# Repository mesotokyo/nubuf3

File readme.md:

# MST DRIVE (Nutube Powered Booster/Overdrive) schematic and PCB for KiCAD

(Japanese version is [here](readme_ja.md) / 日本語版は[こちら](readme_ja.md))

## What is this?

KiCAD files to build PCB of the MST DRIVE (Nutube Powered Booster/Overdive). These files are created with KiCad 6.0.

For more information about MST DRIVE, please check https://meso.tokyo/works/drive .

## Notice

 * This schematic and PCB file need a `ak_misc` footprint library in [mst-kicad-lib](https://github.com/mesotokyo/mst-kicad-lib). 
 * It is assumed that this schematic will be used with [voltboost2e](https://github.com/mesotokyo/voltboost2e) DC-DC converter unit.

## DISCLAIMER

FILES IN THIS REPOSITORY ARE PROVIDED "AS IS", WITHOUT WARRANTY OF ANY KIND, EXPRESS OR IMPLIED, INCLUDING BUT NOT LIMITED TO THE WARRANTIES OF MERCHANTABILITY, FITNESS FOR A PARTICULAR PURPOSE AND NONINFRINGEMENT. IN NO EVENT SHALL THE AUTHORS OR COPYRIGHT HOLDERS BE LIABLE FOR ANY CLAIM, DAMAGES OR OTHER LIABILITY, WHETHER IN AN ACTION OF CONTRACT, TORT OR OTHERWISE, ARISING FROM, OUT OF OR IN CONNECTION WITH IN FILES IN THIS REPOSITORY OR THE USE OR OTHER DEALINGS IN FILES IN THIS REPOSITORY.

## License

CC BY 4.0. For more information, please check https://creativecommons.org/licenses/by/4.0/ .

## Author

MST/mesotokyo

 - https://meso.tokyo/
 - https://x.com/mesotokyox

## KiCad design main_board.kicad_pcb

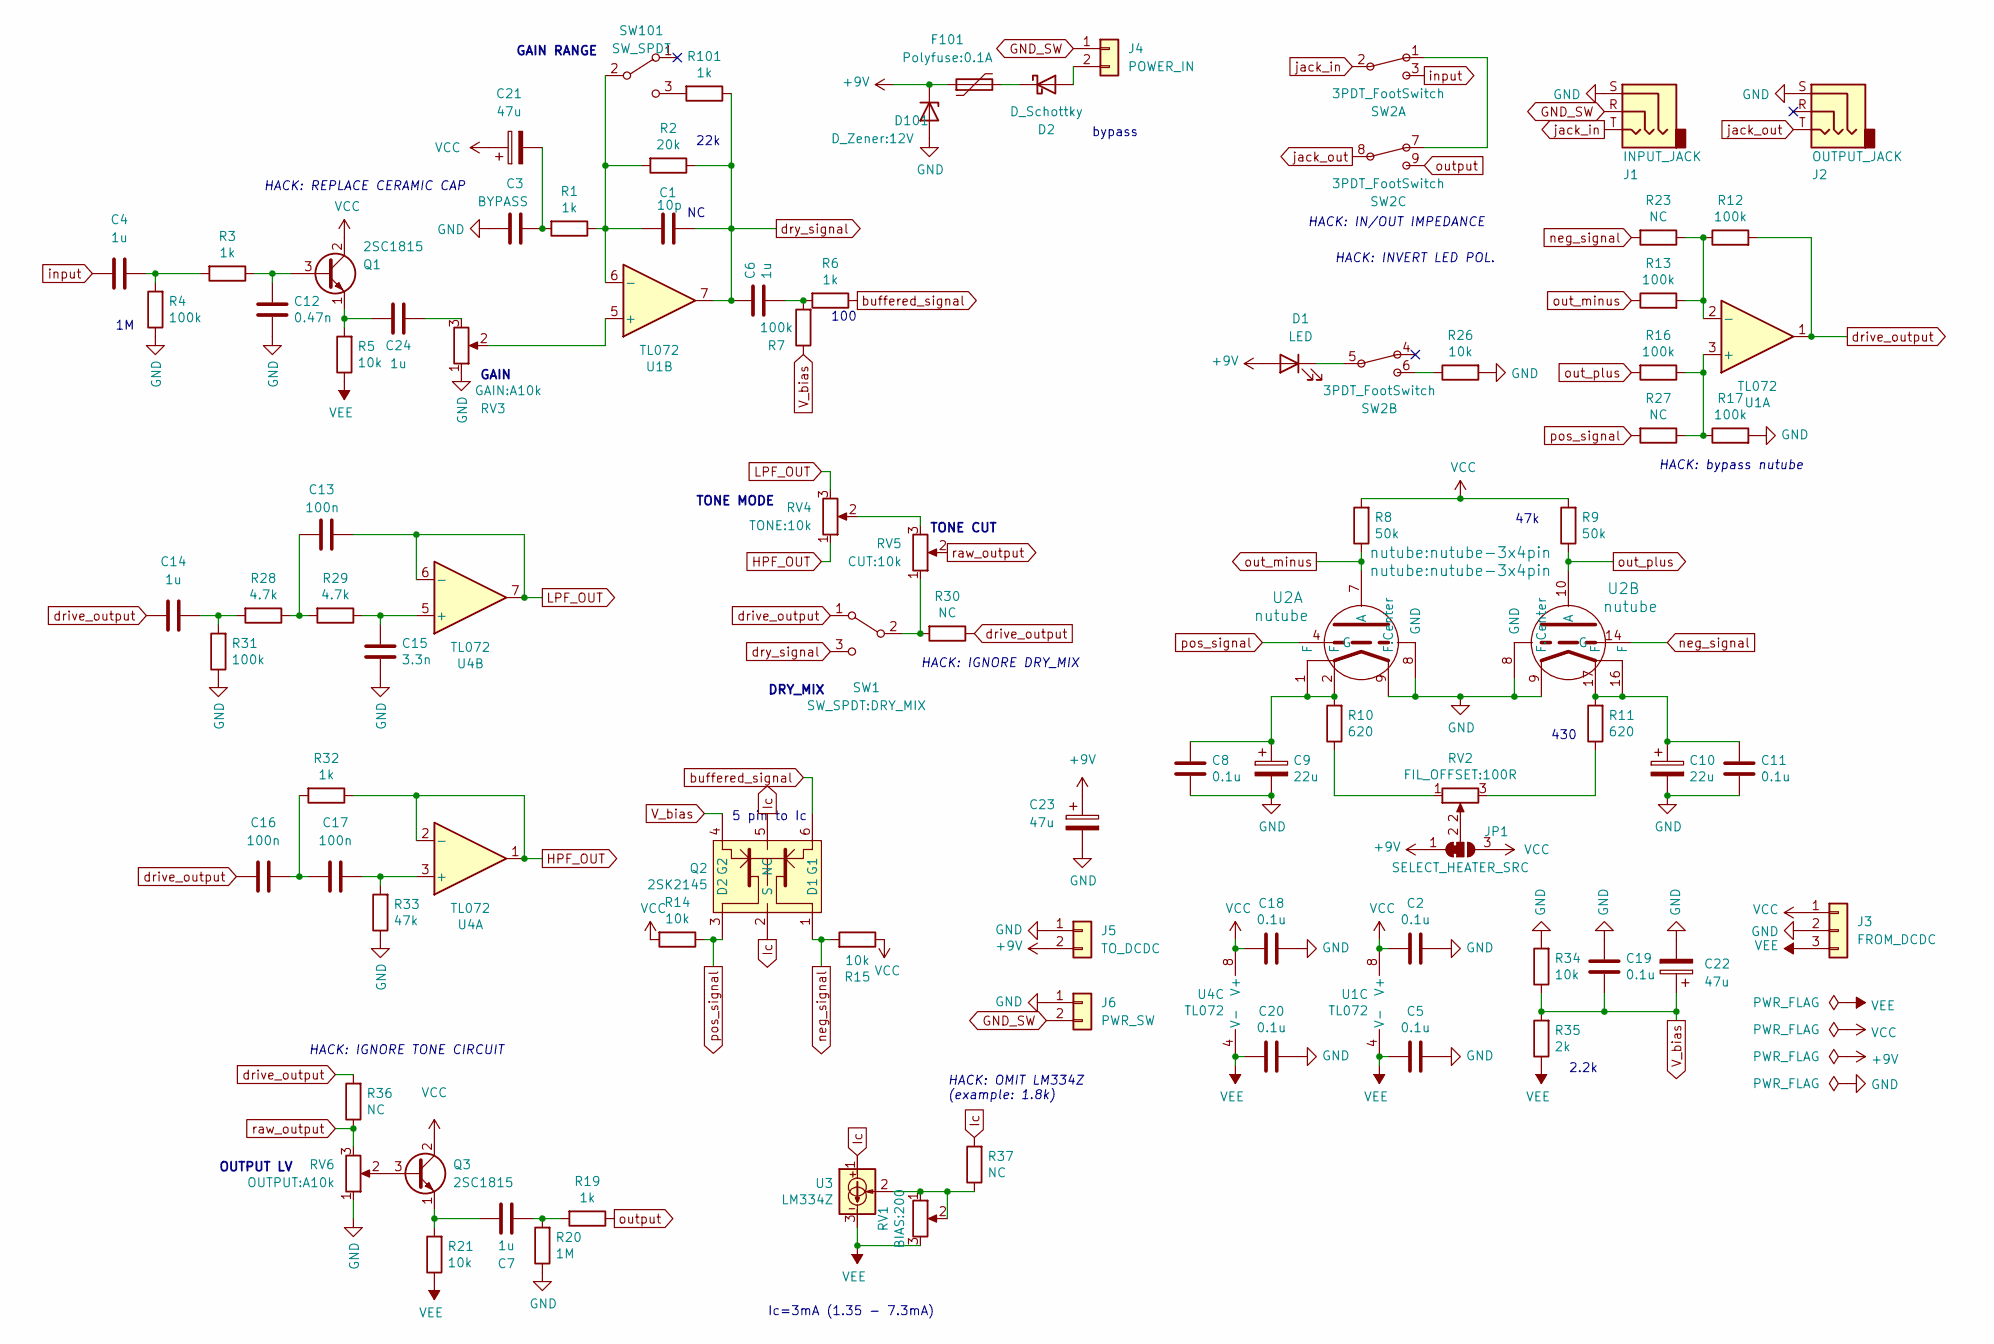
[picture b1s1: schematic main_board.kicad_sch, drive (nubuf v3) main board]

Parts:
C1: 10p; C_Disc_D3.0mm_W1.6mm_P2.50mm
C2, C5, C8, C11, C18, C19, C20: 0.1u; C_Disc_D3.0mm_W1.6mm_P2.50mm
C3: BYPASS; C_Disc_D10.5mm_W5.0mm_P5.00mm
C4, C6, C7, C14, C24: 1u; C_Rect_L7.2mm_W7.2mm_P5.00mm_with_SMD_3216
C9, C10: 22u; CP_Radial_D6.3mm_P2.50mm
C12: 0.47n; C_Rect_F2D_L6.0mm_W3.0mm_P3.50mm
C13, C16, C17: 100n; C_Rect_L7.0mm_W2.5mm_P5.00mm
C15: 3.3n; C_Rect_F2D_L6.0mm_W3.0mm_P3.50mm
C21: 47u; CP_EIA-7343-15_Kemet-W_Pad2.25x2.55mm_HandSolder
C22, C23: 47u; CP_Radial_D8.0mm_P3.50mm
D1: LED; LED_D3.0mm
D2: D_Schottky; D_DO-41_SOD81_P10.16mm_Horizontal
D101: D_Zener:12V; D_DO-41_SOD81_P7.62mm_Horizontal
F101: Polyfuse:0.1A; C_Disc_D4.3mm_W1.9mm_P5.00mm
J1: INPUT_JACK; MJ-187
J2: OUTPUT_JACK; MJ-187
J3: FROM_DCDC; JST_XH_B3B-XH-A_1x03_P2.50mm_Vertical
J4: POWER_IN; JST_XH_B2B-XH-A_1x02_P2.50mm_Vertical
J5: TO_DCDC; JST_XH_B2B-XH-A_1x02_P2.50mm_Vertical
J6: PWR_SW; PinHeader_1x02_P2.54mm_Vertical
JP1: SELECT_HEATER_SRC; SolderJumper-3_P1.3mm_Bridged12_RoundedPad1.0x1.5mm
Q1, Q3: 2SC1815; TO-92_Inline_Wide
Q2: 2SK2145; DIP-6_W7.62mm
R1, R3, R6, R19, R32, R101: 1k; R_Axial_DIN0207_L6.3mm_D2.5mm_P7.62mm_with_SMD
R2: 20k; R_Axial_DIN0207_L6.3mm_D2.5mm_P7.62mm_with_SMD
R4, R7, R12, R13, R16, R17, R31: 100k; R_Axial_DIN0207_L6.3mm_D2.5mm_P7.62mm_with_SMD
R5, R14, R15, R21, R26, R34: 10k; R_Axial_DIN0207_L6.3mm_D2.5mm_P7.62mm_with_SMD
R8, R9: 50k; R_Axial_DIN0207_L6.3mm_D2.5mm_P7.62mm_with_SMD
R10, R11: 620; R_Axial_DIN0207_L6.3mm_D2.5mm_P7.62mm_with_SMD
R20: 1M; R_Axial_DIN0207_L6.3mm_D2.5mm_P7.62mm_with_SMD
R23, R27, R30, R36, R37: NC; R_Axial_DIN0207_L6.3mm_D2.5mm_P7.62mm_with_SMD
R28, R29: 4.7k; R_Axial_DIN0207_L6.3mm_D2.5mm_P7.62mm_with_SMD
R33: 47k; R_Axial_DIN0207_L6.3mm_D2.5mm_P7.62mm_with_SMD
R35: 2k; R_Axial_DIN0207_L6.3mm_D2.5mm_P7.62mm_with_SMD
RV1: BIAS:200; GF063
RV2: FIL_OFFSET:100R; GF063
RV3: GAIN:A10k; POT-16mm
RV4: TONE:10k; POT-16mm
RV5: CUT:10k; POT-16mm
RV6: OUTPUT:A10k; POT-16mm
SW1: SW_SPDT:DRY_MIX; spdt-sw-micro
SW2: 3PDT_FootSwitch
SW101: SW_SPDT; spdt-sw-micro
U1, U4: TL072; DIP-8_W7.62mm
U2: nutube; nutube-3x4pin
U3: LM334Z; TO-92L_Inline_Wide

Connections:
+9V: C23.1, D1.2 (A), D101.1 (K), F101.1, J5.2, JP1.1 (A)
GND: C2.1, C3.1, C5.1, C8.2, C9.2, C10.2, C11.2, C12.2, C15.2, C18.1, C19.1, C20.1, C22.2, C23.2, D101.2 (A), J1.S, J2.S, J3.2, J5.1, J6.1, R4.1, R17.2, R20.1, R26.2, R31.1, R33.1, R34.2, RV3.1, RV6.1, U2.8 (GND), U2.9 (F.Center)
GND_SW: J1.R, J4.1, J6.2
HPF_OUT: R32.1, RV4.1, U4.1, U4.2 (-)
Ic: Q2.2 (S), Q2.5 (NC), R37.2, U3.1
LPF_OUT: C13.2, RV4.3, U4.6 (-), U4.7
unnamed: C1.1, R1.1, R2.2, SW101.2 (B), U1.6 (-)
unnamed: C4.2, R3.2, R4.2
unnamed: C6.2, R6.2, R7.2
unnamed: C7.1, Q3.1 (E), R21.2
unnamed: C7.2, R19.2, R20.2
unnamed: C8.1, C9.1, R10.2, U2.1 (F), U2.2 (F)
unnamed: C10.1, C11.1, R11.2, U2.16 (F), U2.17 (F)
unnamed: C12.1, Q1.3 (B), R3.1
unnamed: C13.1, R28.1, R29.2
unnamed: C14.2, R28.2, R31.2
unnamed: C15.1, R29.1, U4.5 (+)
unnamed: C16.2, C17.1, R32.2
unnamed: C17.2, R33.2, U4.3 (+)
unnamed: C3.2, C21.2, R1.2
unnamed: C24.1, Q1.1 (E), R5.2
unnamed: C24.2, RV3.3
unnamed: D1.1 (K), SW2.5
unnamed: D2.1 (K), F101.2
unnamed: D2.2 (A), J4.2
unnamed: JP1.2 (C), RV2.2
unnamed: Q3.3 (B), RV6.2
unnamed: R10.1, RV2.1
unnamed: R11.1, RV2.3
unnamed: R12.1, R13.2, R23.1, U1.2 (-)
unnamed: R16.1, R17.1, R27.1, U1.3 (+)
unnamed: R26.1, SW2.6
unnamed: R30.2, RV5.1, SW1.2 (B)
unnamed: R37.1, RV1.1, RV1.2, U3.2
unnamed: R101.2, SW101.3 (C)
unnamed: RV3.2, U1.5 (+)
unnamed: RV4.2, RV5.3
unnamed: SW2.1, SW2.7
VCC: C2.2, C18.2, C21.1, J3.1, JP1.3 (B), Q1.2 (C), Q3.2 (C), R8.2, R9.2, R14.2, R15.1, U1.8 (V+), U4.8 (V+)
VEE: C5.2, C20.2, J3.3, R5.1, R21.1, R35.1, RV1.3, U1.4 (V-), U3.3, U4.4 (V-)
V_bias: C19.2, C22.1, Q2.4 (G2), R7.1, R34.1, R35.2
buffered_signal: Q2.6 (G1), R6.1
drive_output: C14.1, C16.1, R12.2, R30.1, R36.2, SW1.1 (A), U1.1
dry_signal: C1.2, C6.1, R2.1, R101.1, SW1.3 (C), U1.7
input: C4.1, SW2.3
jack_in: J1.T, SW2.2
jack_out: J2.T, SW2.8
neg_signal: Q2.1 (D1), R15.2, R23.2, U2.14 (G)
out_minus: R8.1, R13.1, U2.7 (A)
out_plus: R9.1, R16.2, U2.10 (A)
output: R19.1, SW2.9
pos_signal: Q2.3 (D2), R14.1, R27.2, U2.4 (G)
raw_output: R36.1, RV5.2, RV6.3

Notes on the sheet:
GAIN RANGE
GAIN
HACK: REPLACE CERAMIC CAP
HACK: OMIT LM334Z (example: 1.8k)
TONE MODE
HACK: bypass nutube
DRY_MIX
5 pin to Ic
TONE CUT
HACK: INVERT LED POL.
bypass
Ic=3mA (1.35 - 7.3mA)
47k
100
HACK: IN/OUT IMPEDANCE
430
HACK: IGNORE TONE CIRCUIT
OUTPUT LV
22k
2.2k
HACK: IGNORE DRY_MIX

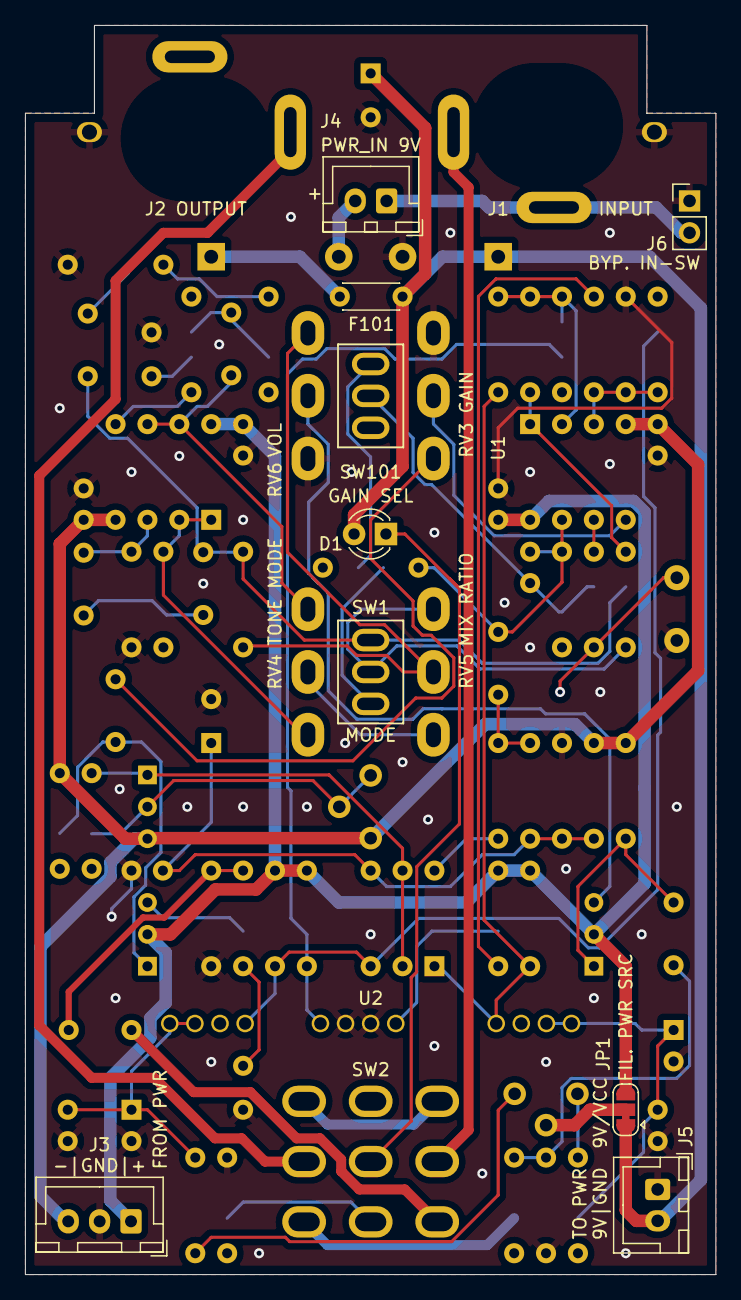
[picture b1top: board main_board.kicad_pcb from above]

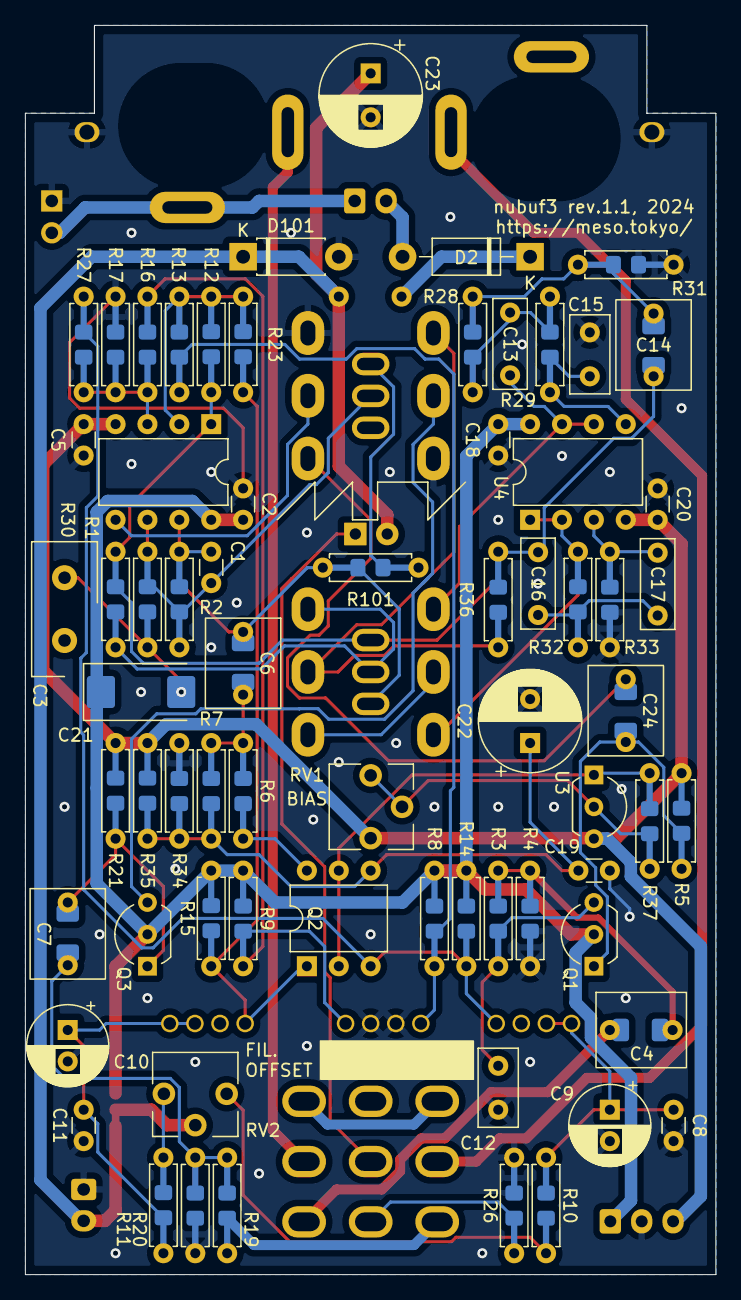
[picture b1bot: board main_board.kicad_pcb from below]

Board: 2 copper layers, 55.0 x 99.5 mm, 85 parts (68 on the bottom side), 53 nets.

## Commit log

2024-09-13 fix URL typo in readme
